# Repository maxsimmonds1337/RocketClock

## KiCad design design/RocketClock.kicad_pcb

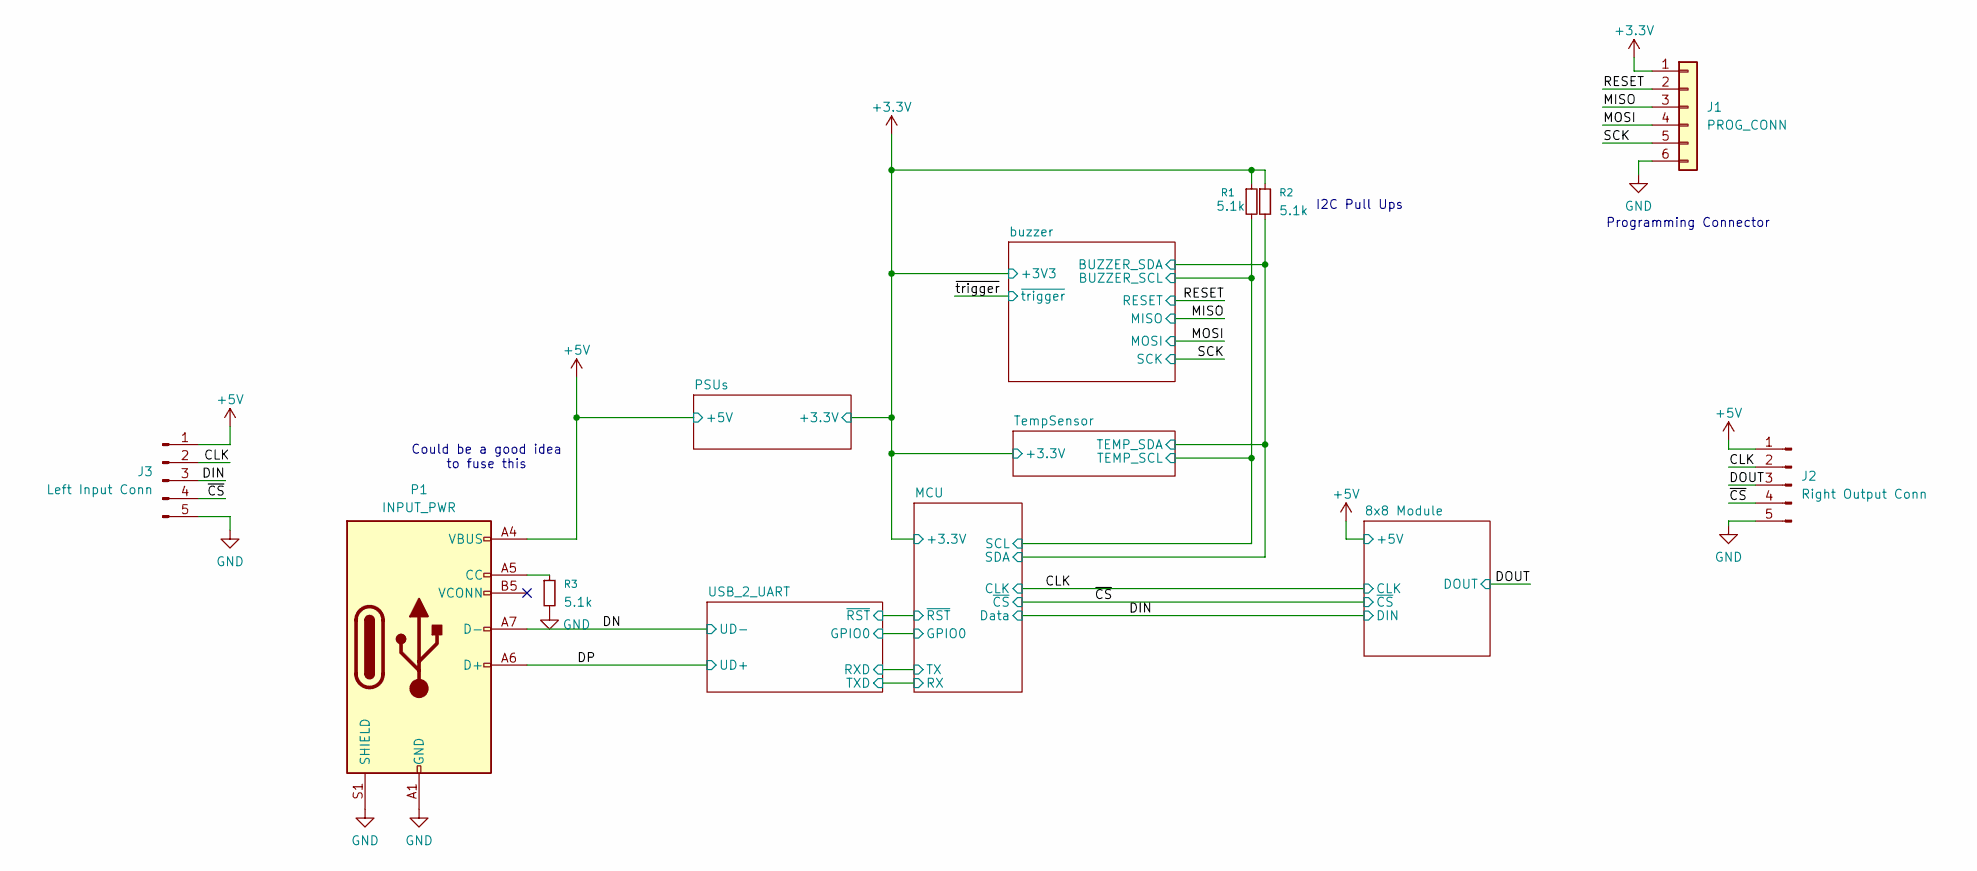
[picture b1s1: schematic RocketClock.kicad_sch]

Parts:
J1: PROG_CONN; PinHeader_1x06_P1.00mm_Vertical_SMD_Pin1Left
J2: Right Output Conn; MagConn
J3: Left Input Conn; MagConn
P1: INPUT_PWR; USB_C_Receptacle_GCT_USB4105-xx-A_16P_TopMnt_Horizontal
R1, R2, R3: 5.1k; R_0402_1005Metric_Pad0.72x0.64mm_HandSolder

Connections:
+3.3V: J1.1, R1.1, R2.1; also elsewhere on the board
+5V: J2.1, J3.1, P1.A4 (VBUS), P1.A9 (VBUS), P1.B4 (VBUS), P1.B9 (VBUS); also elsewhere on the board
/CLK: J2.2, J3.2; also elsewhere on the board
/DIN: J3.3; also elsewhere on the board
/DN: P1.A7 (D-); also elsewhere on the board
/DOUT: J2.3; also elsewhere on the board
/DP: P1.A6 (D+); also elsewhere on the board
/MISO: J1.3; also elsewhere on the board
/MOSI: J1.4; also elsewhere on the board
/RESET: J1.2; also elsewhere on the board
/SCK: J1.5; also elsewhere on the board
/buzzer/SCL: R1.2; also elsewhere on the board
/buzzer/SDA: R2.2; also elsewhere on the board
/~CS: J2.4, J3.4; also elsewhere on the board
GND: J1.6, J2.5, J3.5, P1.A1 (GND), P1.A12 (GND), P1.B1 (GND), P1.B12 (GND), P1.S1 (SHIELD), R3.2; also elsewhere on the board
unnamed: P1.A5 (CC), R3.1

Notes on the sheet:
Could be a good idea to fuse this
I2C Pull Ups
Programming Connector

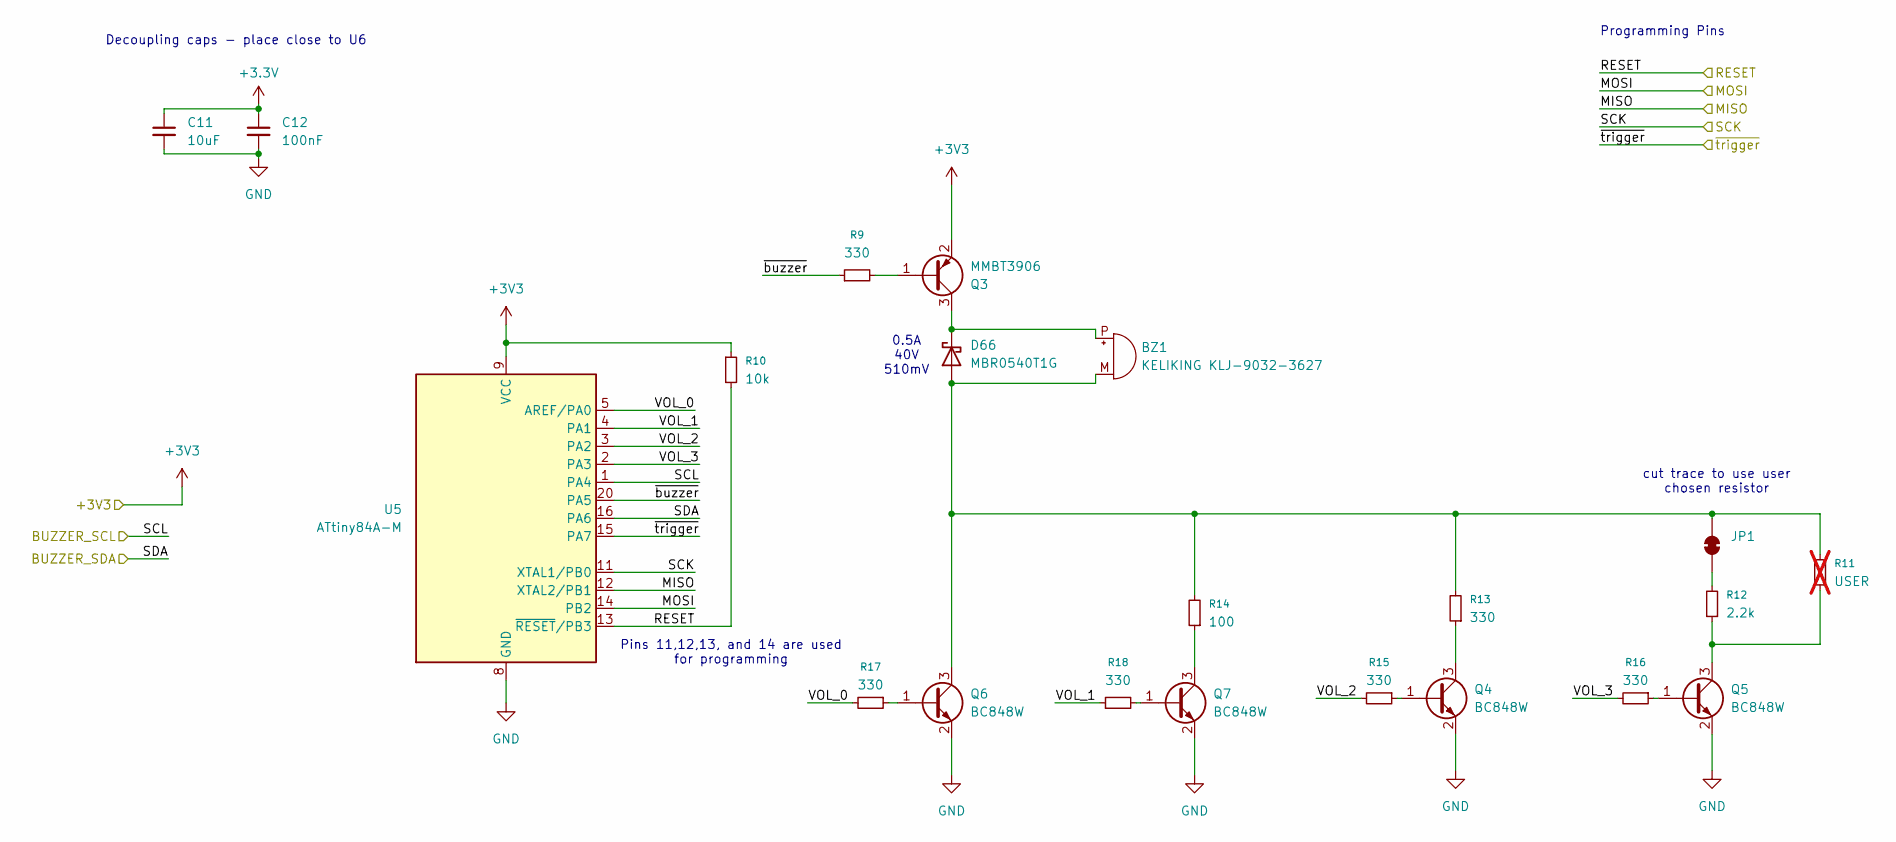
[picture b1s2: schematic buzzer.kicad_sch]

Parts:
BZ1: KELIKING KLJ-9032-3627; CUI_CBT-09427-SMT
C11: 10uF; C_0402_1005Metric_Pad0.74x0.62mm_HandSolder
C12: 100nF; C_0402_1005Metric_Pad0.74x0.62mm_HandSolder
D66: MBR0540T1G; D_SOD-123
JP1: SolderJumper_2_Bridged; SolderJumper-2_P1.3mm_Bridged2Bar_RoundedPad1.0x1.5mm
Q3: MMBT3906; SOT-23
Q4, Q5, Q6, Q7: BC848W; SOT-323_SC-70
R9, R13, R15, R16, R17, R18: 330; R_0402_1005Metric_Pad0.72x0.64mm_HandSolder
R10: 10k; R_0402_1005Metric_Pad0.72x0.64mm_HandSolder
R11: USER; R_0402_1005Metric_Pad0.72x0.64mm_HandSolder; not fitted
R12: 2.2k; R_0402_1005Metric_Pad0.72x0.64mm_HandSolder
R14: 100; R_0402_1005Metric_Pad0.72x0.64mm_HandSolder
U5: ATtiny84A-M; QFN-20-1EP_4x4mm_P0.5mm_EP2.6x2.6mm

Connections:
+3.3V: C11.1, C12.1, Q3.2 (E), R10.1, U5.9 (VCC); also elsewhere on the board
/MISO: U5.12 (XTAL2/PB1); also elsewhere on the board
/MOSI: U5.14 (PB2); also elsewhere on the board
/RESET: R10.2, U5.13 (~RESET/PB3); also elsewhere on the board
/SCK: U5.11 (XTAL1/PB0); also elsewhere on the board
/buzzer/SCL: U5.1 (PA4); also elsewhere on the board
/buzzer/SDA: U5.16 (PA6); also elsewhere on the board
/buzzer/VOL_0: R17.2, U5.5 (AREF/PA0)
/buzzer/VOL_1: R18.1, U5.4 (PA1)
/buzzer/VOL_2: R15.2, U5.3 (PA2)
/buzzer/VOL_3: R16.2, U5.2 (PA3)
/buzzer/~buzzer: R9.1, U5.20 (PA5)
/~trigger: U5.15 (PA7)
GND: C11.2, C12.2, Q4.2 (E), Q5.2 (E), Q6.2 (E), Q7.2 (E), U5.8 (GND), U5.21 (GND); also elsewhere on the board
unnamed: BZ1.M, D66.2 (A), JP1.2 (B), Q6.3 (C), R11.2, R13.2, R14.2
unnamed: BZ1.P, D66.1 (K), Q3.3 (C)
unnamed: JP1.1 (A), R12.2
unnamed: Q3.1 (B), R9.2
unnamed: Q4.1 (B), R15.1
unnamed: Q4.3 (C), R13.1
unnamed: Q5.1 (B), R16.1
unnamed: Q5.3 (C), R11.1, R12.1
unnamed: Q6.1 (B), R17.1
unnamed: Q7.1 (B), R18.2
unnamed: Q7.3 (C), R14.1

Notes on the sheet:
Pins 11,12,13, and 14 are used for programming
0.5A 40V 510mV
cut trace to use user chosen resistor
Programming Pins
Decoupling caps - place close to U6

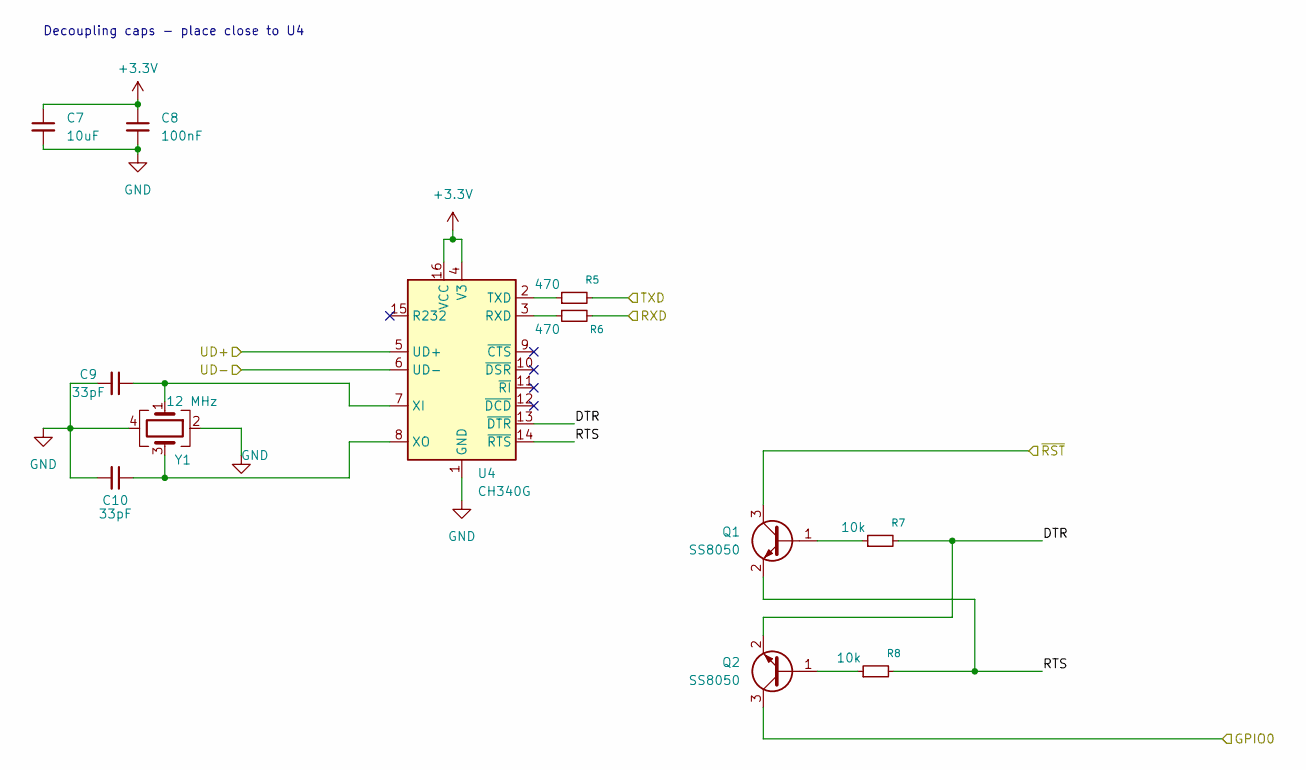
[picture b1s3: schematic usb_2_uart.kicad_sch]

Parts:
C7: 10uF; C_0402_1005Metric_Pad0.74x0.62mm_HandSolder
C8: 100nF; C_0402_1005Metric_Pad0.74x0.62mm_HandSolder
C9, C10: 33pF; C_0402_1005Metric_Pad0.74x0.62mm_HandSolder
Q1, Q2: SS8050; SOT-23
R5, R6: 470; R_0402_1005Metric_Pad0.72x0.64mm_HandSolder
R7, R8: 10k; R_0402_1005Metric_Pad0.72x0.64mm_HandSolder
U4: CH340G; SOIC-16_3.9x9.9mm_P1.27mm
Y1: 12 MHz; Crystal_SMD_3225-4Pin_3.2x2.5mm_HandSoldering

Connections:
+3.3V: C7.1, C8.1, U4.4 (V3), U4.16 (VCC); also elsewhere on the board
/DN: U4.6 (UD-); also elsewhere on the board
/DP: U4.5 (UD+); also elsewhere on the board
/MCU/GPIO0: Q2.3 (C); also elsewhere on the board
/MCU/RX: R5.2; also elsewhere on the board
/MCU/TX: R6.2; also elsewhere on the board
/MCU/~RST: Q1.3 (C); also elsewhere on the board
/USB_2_UART/DTR: Q2.2 (E), R7.2, U4.13 (~DTR)
/USB_2_UART/RTS: Q1.2 (E), R8.2, U4.14 (~RTS)
GND: C7.2, C8.2, C9.2, C10.2, U4.1 (GND), Y1.2, Y1.4; also elsewhere on the board
unnamed: Q1.1 (B), R7.1
unnamed: Q2.1 (B), R8.1
unnamed: R6.1, U4.3 (RXD)
unnamed: R5.1, U4.2 (TXD)
unnamed: C9.1, U4.7 (XI), Y1.1
unnamed: C10.1, U4.8 (XO), Y1.3

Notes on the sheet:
Decoupling caps - place close to U4

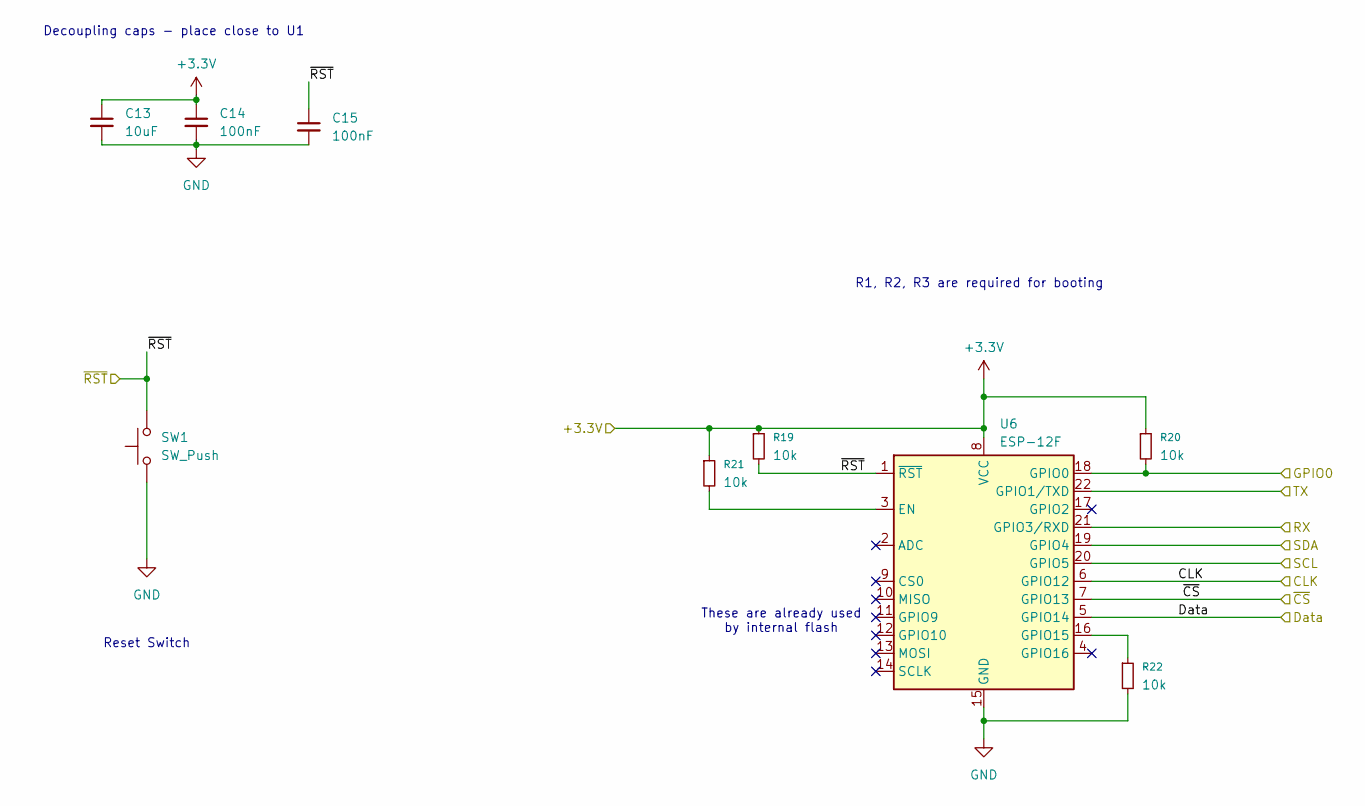
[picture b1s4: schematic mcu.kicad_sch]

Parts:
C13: 10uF; C_0402_1005Metric_Pad0.74x0.62mm_HandSolder
C14, C15: 100nF; C_0402_1005Metric_Pad0.74x0.62mm_HandSolder
R19, R20, R21, R22: 10k; R_0402_1005Metric_Pad0.72x0.64mm_HandSolder
SW1: SW_Push; SW_Push_1P1T_NO_CK_KSC6xxJ
U6: ESP-12F; ESP-12E

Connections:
+3.3V: C13.1, C14.1, R19.1, R20.1, R21.1, U6.8 (VCC); also elsewhere on the board
/CLK: U6.6 (GPIO12); also elsewhere on the board
/DIN: U6.5 (GPIO14); also elsewhere on the board
/MCU/GPIO0: R20.2, U6.18 (GPIO0); also elsewhere on the board
/MCU/RX: U6.21 (GPIO3/RXD); also elsewhere on the board
/MCU/TX: U6.22 (GPIO1/TXD); also elsewhere on the board
/MCU/~RST: C15.1, R19.2, SW1.2, U6.1 (~RST); also elsewhere on the board
/buzzer/SCL: U6.20 (GPIO5); also elsewhere on the board
/buzzer/SDA: U6.19 (GPIO4); also elsewhere on the board
/~CS: U6.7 (GPIO13); also elsewhere on the board
GND: C13.2, C14.2, C15.2, R22.2, SW1.1, U6.15 (GND); also elsewhere on the board
unnamed: R21.2, U6.3 (EN)
unnamed: R22.1, U6.16 (GPIO15)

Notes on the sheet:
Reset Switch
These are already used by internal flash
Decoupling caps - place close to U1
R1, R2, R3 are required for booting

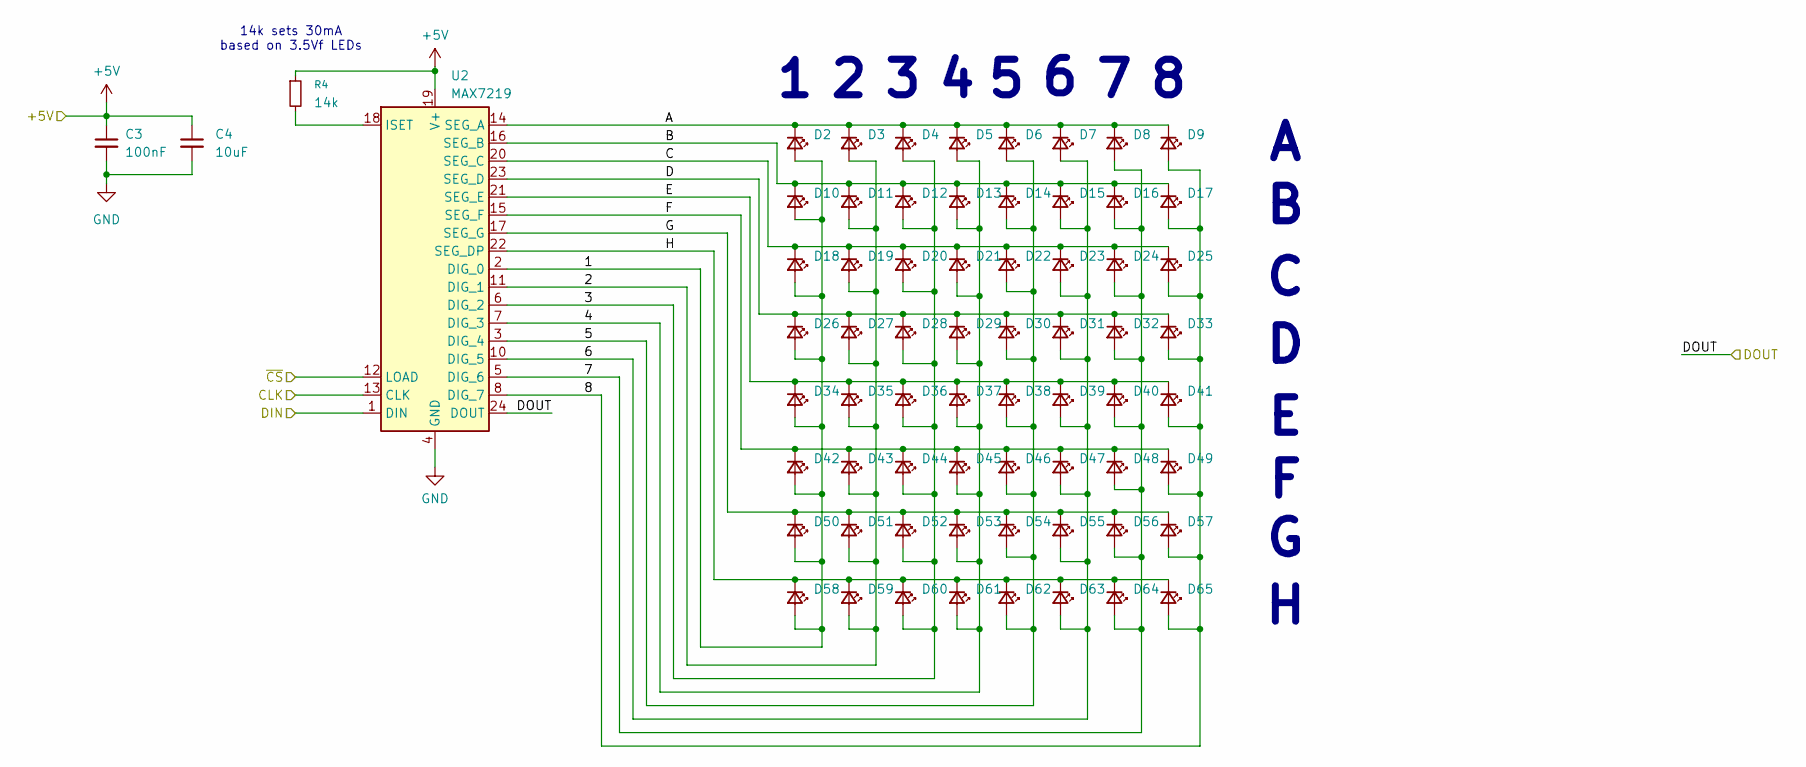
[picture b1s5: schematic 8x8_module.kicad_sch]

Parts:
C3: 100nF; C_0402_1005Metric_Pad0.74x0.62mm_HandSolder
C4: 10uF; C_0402_1005Metric_Pad0.74x0.62mm_HandSolder
D2, D3, D4, D5, D6, D7, D8, D9, D10, D11, D12, D13, D14, D15, D16, D17, D18, D19, D20, D21, D22, D23, D24, D25, D26, D27, D28, D29, D30, D31, D32, D33, D34, D35, D36, D37, D38, D39, D40, D41, D42, D43, D44, D45, D46, D47, D48, D49, D50, D51, D52, D53, D54, D55, D56, D57, D58, D59, D60, D61, D62, D63, D64, D65: Green; LED_0805_2012Metric_Pad1.15x1.40mm_HandSolder
R4: 14k; R_0402_1005Metric_Pad0.72x0.64mm_HandSolder
U2: MAX7219; SOIC-24W_7.5x15.4mm_P1.27mm

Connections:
+5V: C3.1, C4.1, R4.1, U2.19 (V+); also elsewhere on the board
/8x8 Module/1: D2.2 (A), D10.2 (A), D18.2 (A), D26.2 (A), D34.2 (A), D42.2 (A), D50.2 (A), D58.2 (A), U2.2 (DIG_0)
/8x8 Module/2: D3.2 (A), D11.2 (A), D19.2 (A), D27.2 (A), D35.2 (A), D43.2 (A), D51.2 (A), D59.2 (A), U2.11 (DIG_1)
/8x8 Module/3: D4.2 (A), D12.2 (A), D20.2 (A), D28.2 (A), D36.2 (A), D44.2 (A), D52.2 (A), D60.2 (A), U2.6 (DIG_2)
/8x8 Module/4: D5.2 (A), D13.2 (A), D21.2 (A), D29.2 (A), D37.2 (A), D45.2 (A), D53.2 (A), D61.2 (A), U2.7 (DIG_3)
/8x8 Module/5: D6.2 (A), D14.2 (A), D22.2 (A), D30.2 (A), D38.2 (A), D46.2 (A), D54.2 (A), D62.2 (A), U2.3 (DIG_4)
/8x8 Module/6: D7.2 (A), D15.2 (A), D23.2 (A), D31.2 (A), D39.2 (A), D47.2 (A), D55.2 (A), D63.2 (A), U2.10 (DIG_5)
/8x8 Module/7: D8.2 (A), D16.2 (A), D24.2 (A), D32.2 (A), D40.2 (A), D48.2 (A), D56.2 (A), D64.2 (A), U2.5 (DIG_6)
/8x8 Module/8: D9.2 (A), D17.2 (A), D25.2 (A), D33.2 (A), D41.2 (A), D49.2 (A), D57.2 (A), D65.2 (A), U2.8 (DIG_7)
/8x8 Module/A: D2.1 (K), D3.1 (K), D4.1 (K), D5.1 (K), D6.1 (K), D7.1 (K), D8.1 (K), D9.1 (K), U2.14 (SEG_A)
/8x8 Module/B: D10.1 (K), D11.1 (K), D12.1 (K), D13.1 (K), D14.1 (K), D15.1 (K), D16.1 (K), D17.1 (K), U2.16 (SEG_B)
/8x8 Module/C: D18.1 (K), D19.1 (K), D20.1 (K), D21.1 (K), D22.1 (K), D23.1 (K), D24.1 (K), D25.1 (K), U2.20 (SEG_C)
/8x8 Module/D: D26.1 (K), D27.1 (K), D28.1 (K), D29.1 (K), D30.1 (K), D31.1 (K), D32.1 (K), D33.1 (K), U2.23 (SEG_D)
/8x8 Module/E: D34.1 (K), D35.1 (K), D36.1 (K), D37.1 (K), D38.1 (K), D39.1 (K), D40.1 (K), D41.1 (K), U2.21 (SEG_E)
/8x8 Module/F: D42.1 (K), D43.1 (K), D44.1 (K), D45.1 (K), D46.1 (K), D47.1 (K), D48.1 (K), D49.1 (K), U2.15 (SEG_F)
/8x8 Module/G: D50.1 (K), D51.1 (K), D52.1 (K), D53.1 (K), D54.1 (K), D55.1 (K), D56.1 (K), D57.1 (K), U2.17 (SEG_G)
/8x8 Module/H: D58.1 (K), D59.1 (K), D60.1 (K), D61.1 (K), D62.1 (K), D63.1 (K), D64.1 (K), D65.1 (K), U2.22 (SEG_DP)
/CLK: U2.13 (CLK); also elsewhere on the board
/DIN: U2.1 (DIN); also elsewhere on the board
/DOUT: U2.24 (DOUT); also elsewhere on the board
/~CS: U2.12 (LOAD); also elsewhere on the board
GND: C3.2, C4.2, U2.4 (GND), U2.9 (GND); also elsewhere on the board
unnamed: R4.2, U2.18 (ISET)

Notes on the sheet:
14k sets 30mA based on 3.5Vf LEDs

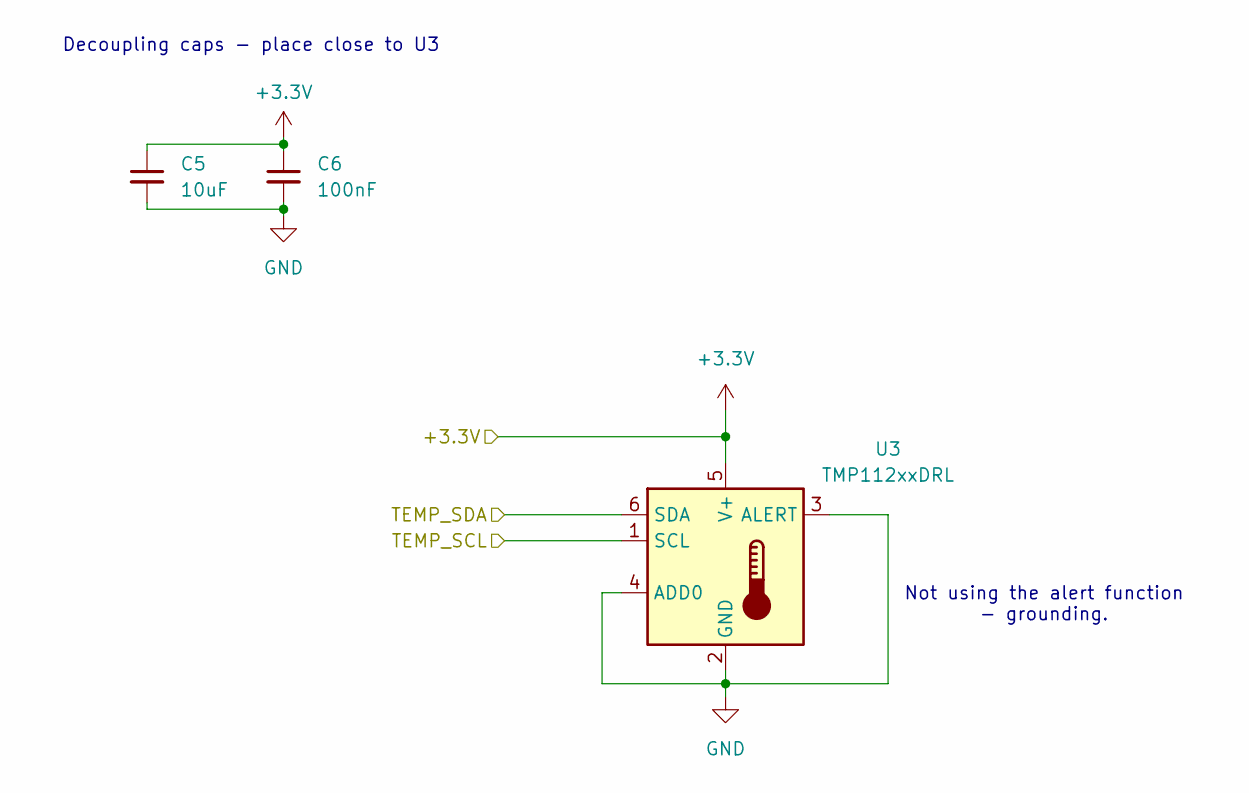
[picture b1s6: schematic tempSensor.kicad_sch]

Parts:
C5: 10uF; C_0402_1005Metric_Pad0.74x0.62mm_HandSolder
C6: 100nF; C_0402_1005Metric_Pad0.74x0.62mm_HandSolder
U3: TMP112xxDRL; SOT-563

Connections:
+3.3V: C5.1, C6.1, U3.5 (V+); also elsewhere on the board
/buzzer/SCL: U3.1 (SCL); also elsewhere on the board
/buzzer/SDA: U3.6 (SDA); also elsewhere on the board
GND: C5.2, C6.2, U3.2 (GND), U3.3 (ALERT), U3.4 (ADD0); also elsewhere on the board

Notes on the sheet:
Not using the alert function - grounding.
Decoupling caps - place close to U3

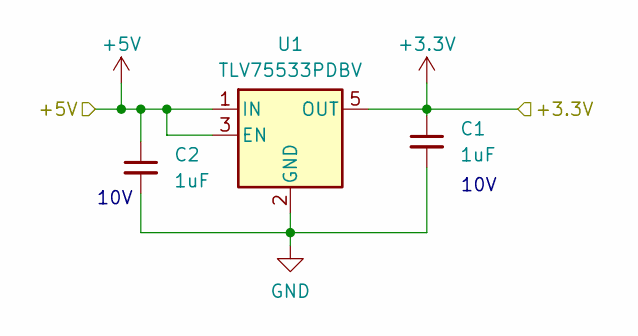
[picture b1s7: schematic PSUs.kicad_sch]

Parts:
C1, C2: 1uF; C_0402_1005Metric_Pad0.74x0.62mm_HandSolder
U1: TLV75533PDBV; SOT-23-5

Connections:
+3.3V: C1.1, U1.5 (OUT); also elsewhere on the board
+5V: C2.1, U1.1 (IN), U1.3 (EN); also elsewhere on the board
GND: C1.2, C2.2, U1.2 (GND); also elsewhere on the board

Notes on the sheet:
10V

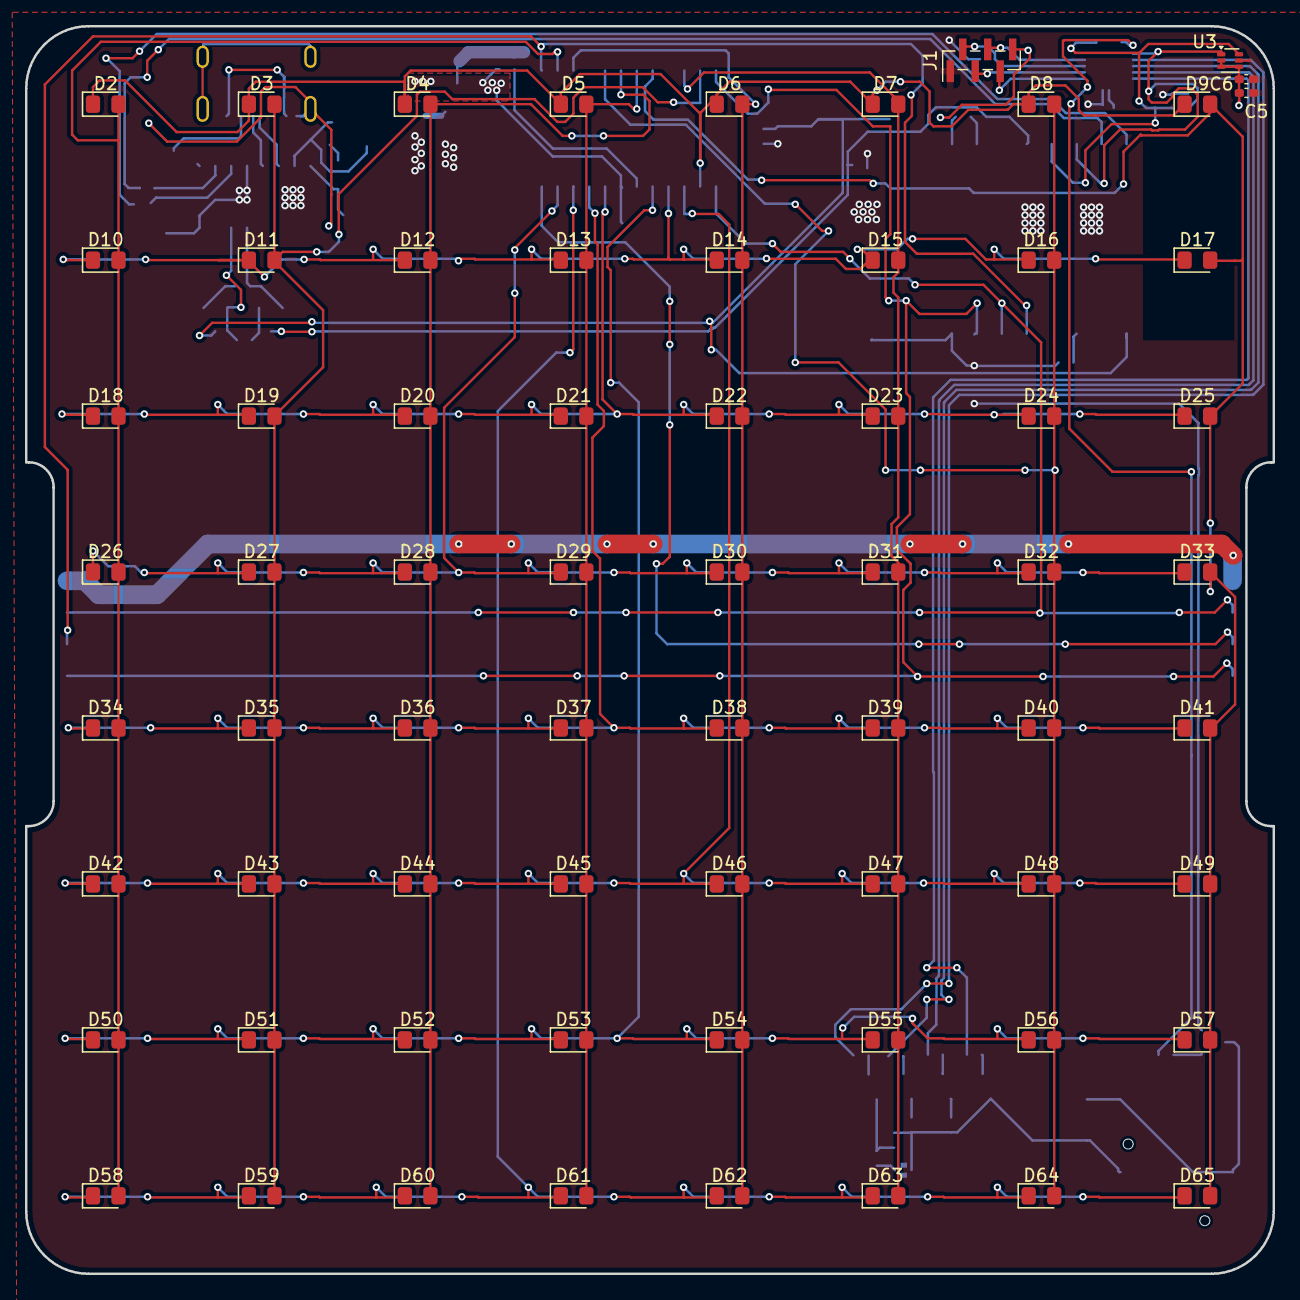
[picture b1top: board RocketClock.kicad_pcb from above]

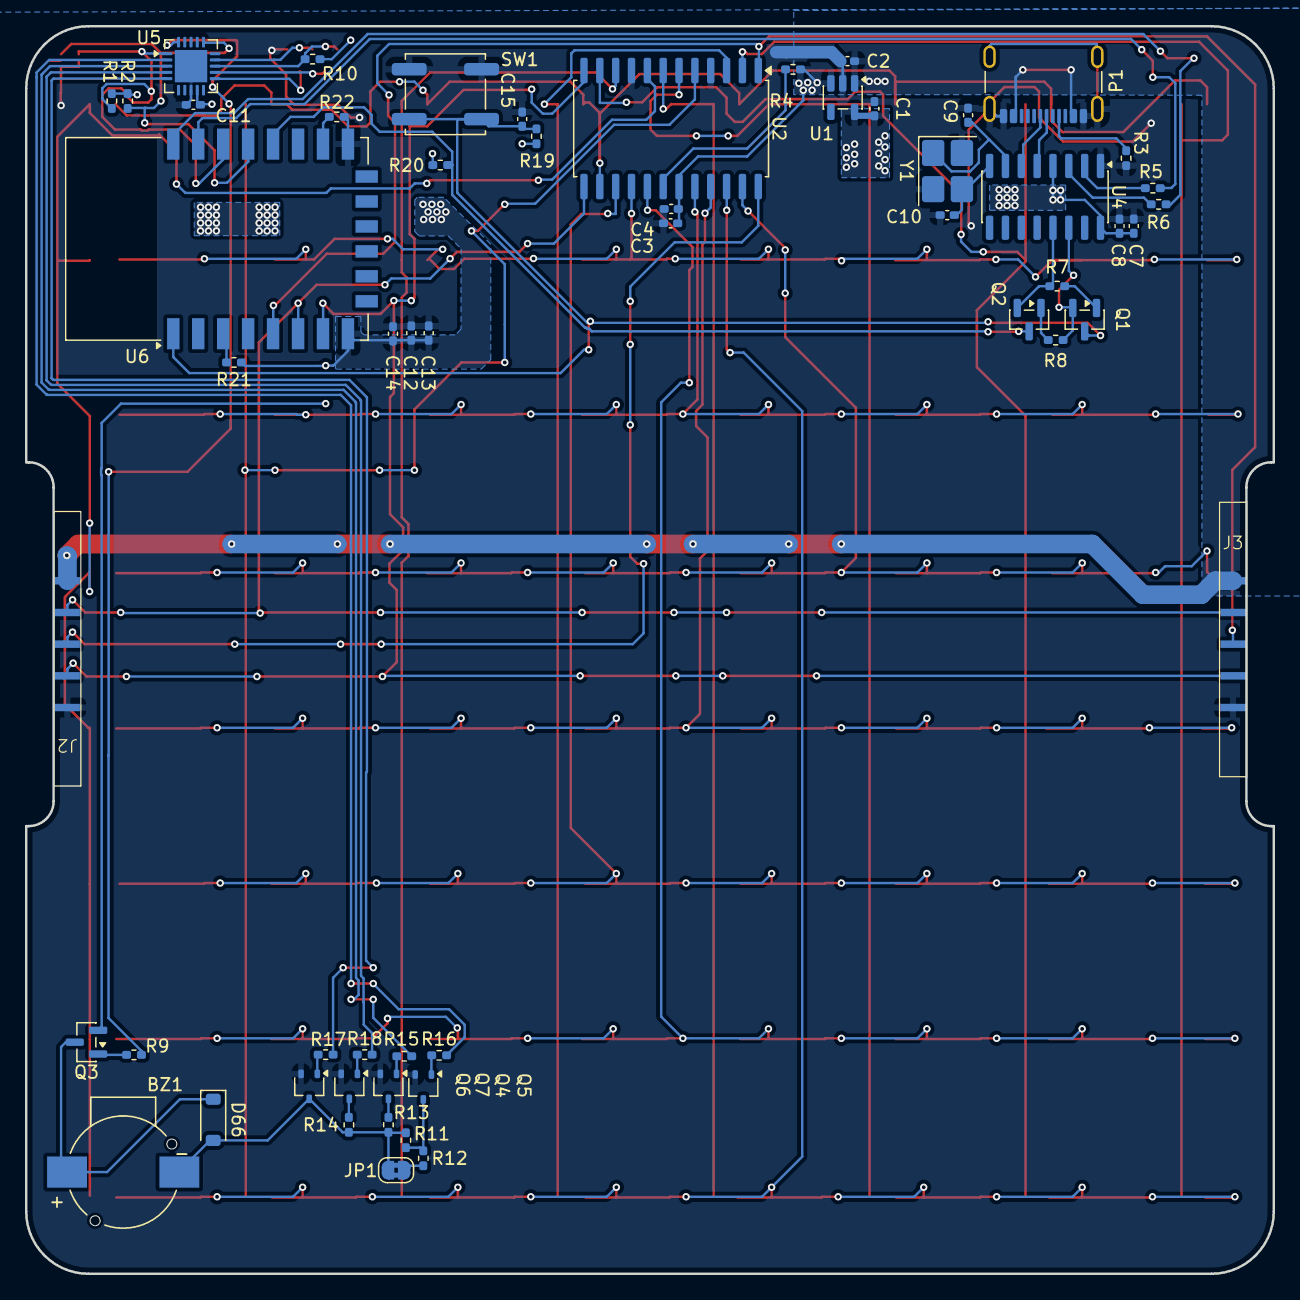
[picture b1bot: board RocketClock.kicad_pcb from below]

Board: 2 copper layers, 100.0 x 100.0 mm, 123 parts (55 on the bottom side), 63 nets.

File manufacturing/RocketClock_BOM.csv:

"Reference","Qty","Value","DNP","Exclude from BOM","Exclude from Board","Footprint","Datasheet"
"BZ1","1","CBT-09427-SMT-TR","","","","footprints:CUI_CBT-09427-SMT","~"
"C1,C2","2","1uF","","","","Capacitor_SMD:C_0402_1005Metric_Pad0.74x0.62mm_HandSolder","~"
"C3,C6,C8,C12,C14,C15","6","100nF","","","","Capacitor_SMD:C_0402_1005Metric_Pad0.74x0.62mm_HandSolder","~"
"C4,C5,C7,C11,C13","5","10uF","","","","Capacitor_SMD:C_0402_1005Metric_Pad0.74x0.62mm_HandSolder","~"
"C9,C10","2","33pF","","","","Capacitor_SMD:C_0402_1005Metric_Pad0.74x0.62mm_HandSolder","~"
"D1,D66","2","D_Schottky","","","","Diode_SMD:D_SOD-123","~"
"D2,D3,D4,D5,D6,D7,D8,D9,D10,D11,D12,D13,D14,D15,D16,D17,D18,D19,D20,D21,D22,D23,D24,D25,D26,D27,D28,D29,D30,D31,D32,D33,D34,D35,D36,D37,D38,D39,D40,D41,D42,D43,D44,D45,D46,D47,D48,D49,D50,D51,D52,D53,D54,D55,D56,D57,D58,D59,D60,D61,D62,D63,D64,D65","64","Green","","","","LED_SMD:LED_0805_2012Metric_Pad1.15x1.40mm_HandSolder","~"
"J1","1","PROG_CONN","","","","Connector_PinHeader_1.00mm:PinHeader_1x06_P1.00mm_Vertical_SMD_Pin1Left","~"
"J2","1","Right Output Conn","","","","Package_SO:MagConn","~"
"J3","1","Left Input Conn","","","","Package_SO:MagConn","~"
"JP1","1","SolderJumper_2_Bridged","","Excluded from BOM","","Jumper:SolderJumper-2_P1.3mm_Bridged2Bar_RoundedPad1.0x1.5mm","~"
"P1","1","INPUT_PWR","","","","Connector_USB:USB_C_Receptacle_GCT_USB4105-xx-A_16P_TopMnt_Horizontal","https://www.usb.org/sites/default/files/documents/usb_type-c.zip"
"Q1,Q2","2","SS8050","","","","Package_TO_SOT_SMD:SOT-23","http://www.secosgmbh.com/datasheet/products/SSMPTransistor/S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"
"Q3","1","MMBT3906","","","","Package_TO_SOT_SMD:SOT-23","https://www.onsemi.com/pdf/datasheet/pzt3906-d.pdf"
"Q4,Q5,Q6,Q7","4","BC848W","","","","Package_TO_SOT_SMD:SOT-323_SC-70","http://www.infineon.com/dgdl/Infineon-BC847SERIES_BC848SERIE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"
"R1,R2,R3","3","5.1k","","","","Resistor_SMD:R_0402_1005Metric_Pad0.72x0.64mm_HandSolder","~"
"R4","1","14k","","","","Resistor_SMD:R_0402_1005Metric_Pad0.72x0.64mm_HandSolder","~"
"R5,R6","2","470","","","","Resistor_SMD:R_0402_1005Metric_Pad0.72x0.64mm_HandSolder","~"
"R7,R8,R10,R19,R20,R21,R22","7","10k","","","","Resistor_SMD:R_0402_1005Metric_Pad0.72x0.64mm_HandSolder","~"
"R9,R13,R15,R16,R17,R18","6","330","","","","Resistor_SMD:R_0402_1005Metric_Pad0.72x0.64mm_HandSolder","~"
"R11","1","USER","DNP","","","Resistor_SMD:R_0402_1005Metric_Pad0.72x0.64mm_HandSolder","~"
"R12","1","2.2k","","","","Resistor_SMD:R_0402_1005Metric_Pad0.72x0.64mm_HandSolder","~"
"R14","1","100","","","","Resistor_SMD:R_0402_1005Metric_Pad0.72x0.64mm_HandSolder","~"
"SW1","1","SW_Push","","","","Button_Switch_SMD:SW_Push_1P1T_NO_CK_KSC6xxJ","~"
"U1","1","TLV75533PDBV","","","","Package_TO_SOT_SMD:SOT-23-5","http://www.ti.com/lit/ds/symlink/tlv755p.pdf"
"U2","1","MAX7219","","","","Package_SO:SOIC-24W_7.5x15.4mm_P1.27mm","https://datasheets.maximintegrated.com/en/ds/MAX7219-MAX7221.pdf"
"U3","1","TMP112xxDRL","","","","Package_TO_SOT_SMD:SOT-563","https://www.ti.com/lit/ds/symlink/tmp112.pdf"
"U4","1","CH340G","","","","Package_SO:SOIC-16_3.9x9.9mm_P1.27mm","http://www.datasheet5.com/pdf-local-2195953"
"U5","1","ATtiny84A-M","","","","Package_DFN_QFN:QFN-20-1EP_4x4mm_P0.5mm_EP2.6x2.6mm","http://ww1.microchip.com/downloads/en/DeviceDoc/doc8183.pdf"
"U6","1","ESP-12F","","","","RF_Module:ESP-12E","http://wiki.ai-thinker.com/_media/esp8266/esp8266_series_mod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"
"Y1","1","12MHz","","","","Crystal:Crystal_SMD_3225-4Pin_3.2x2.5mm_HandSoldering","~"

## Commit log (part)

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2026-02-24 Schematic Capture
    This commit adds the schematic capture (no PCB layout) for the rocket clock. It might change, but this is a first good version.
2026-03-01 Added some more sheets, new board layout
2026-03-16 layout mostly done, schematic is done, need to generate new updated pdf
2026-03-21 Layout and Schematic Done
    Almost ready for first release with tag. DRC etc passing, DFM checks pass on JLCPCB, but I need to go through sourcing components and ensure we have them all available before pushing the button on th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
2026-04-05 added ibom and some software
